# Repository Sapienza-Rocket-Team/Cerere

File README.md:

# Cerere
Avionics board for Medusa 2026

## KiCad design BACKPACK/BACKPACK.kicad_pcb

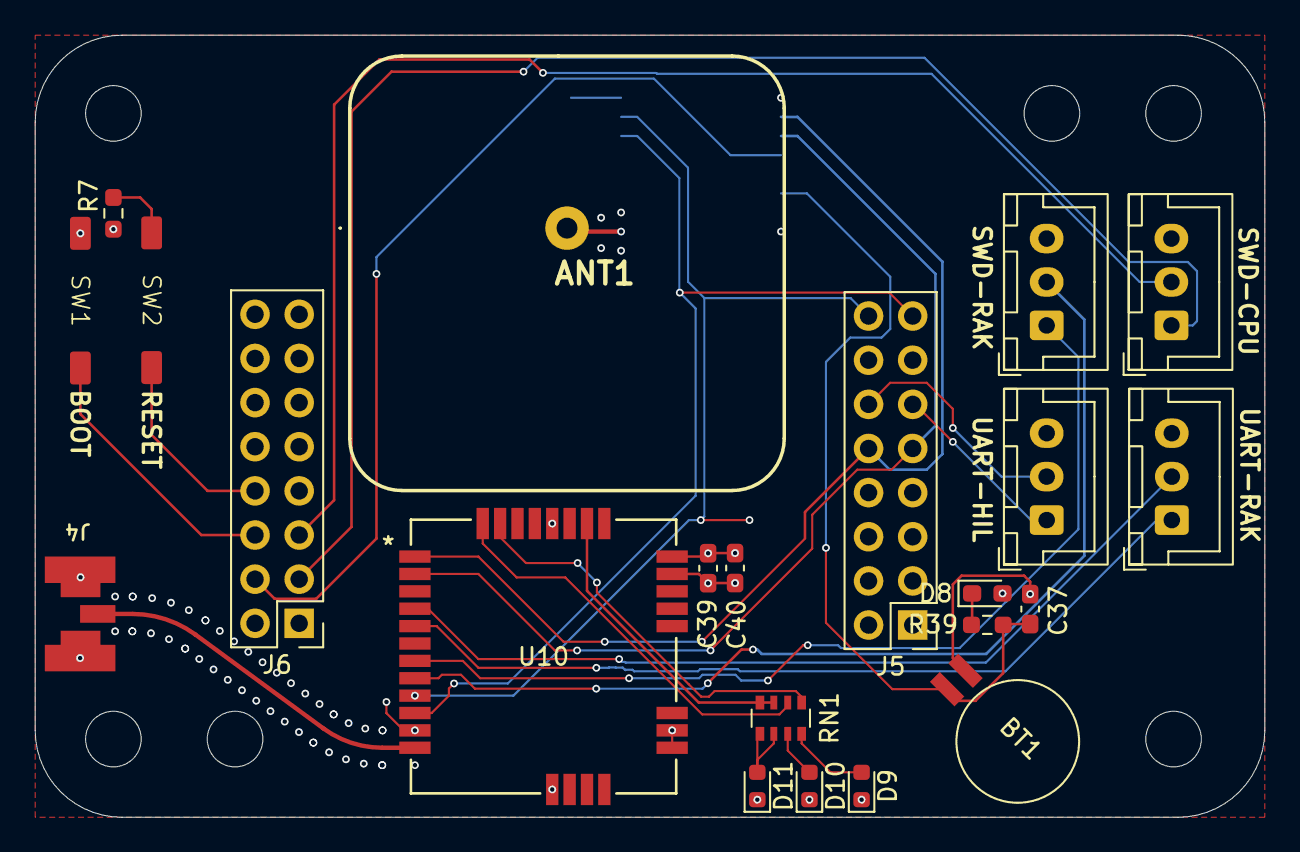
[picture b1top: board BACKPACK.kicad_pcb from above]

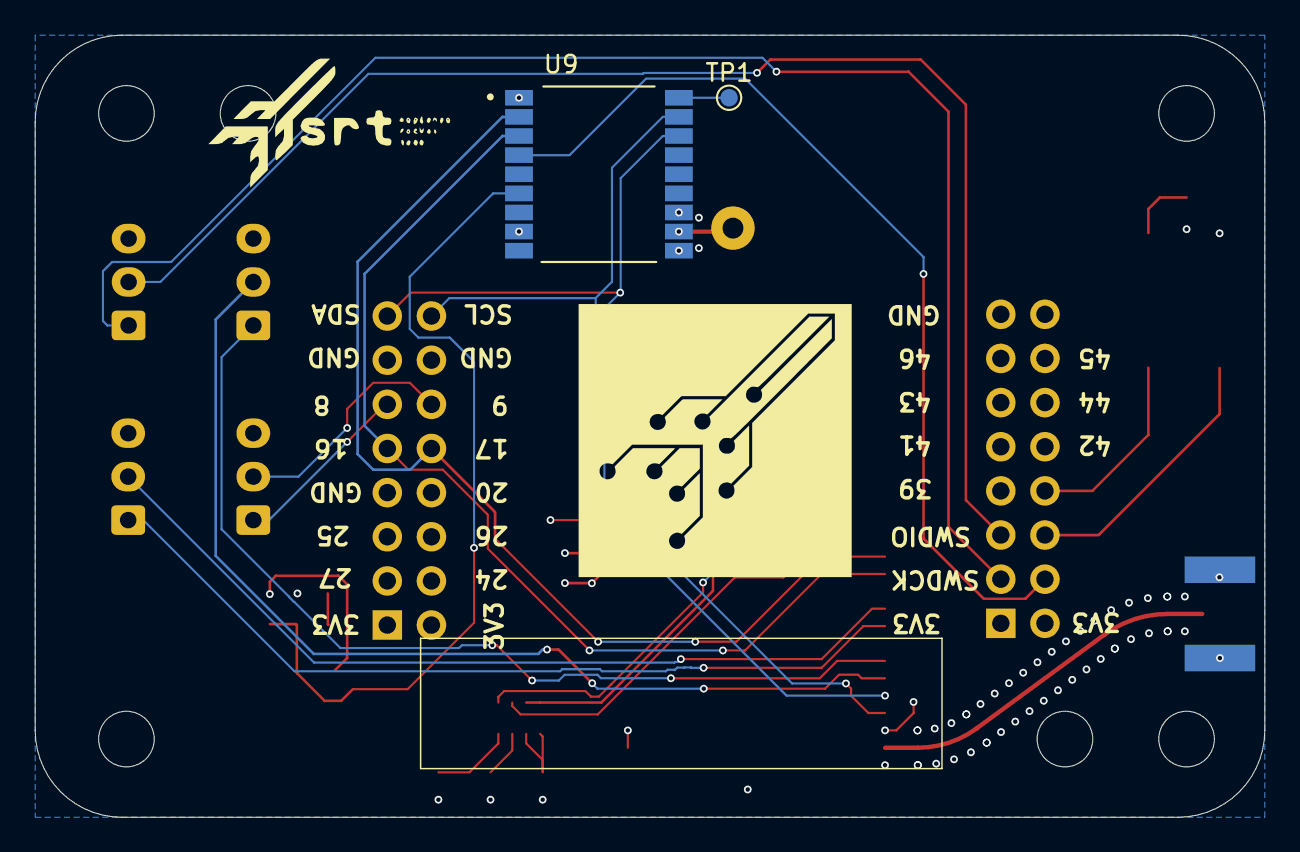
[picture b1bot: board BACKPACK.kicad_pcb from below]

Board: 4 copper layers, 70.8 x 45.0 mm, 30 parts (8 on the bottom side), 29 nets.

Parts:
ANT1: AANI-PP-0055; AANIPP0055
BT1: Battery_Cell; BatteryHolder_Seiko_MS621F
C37, C40: 100nF; C_0603_1608Metric_Pad1.08x0.95mm_HandSolder
C39: 10nF; C_0603_1608Metric_Pad1.08x0.95mm_HandSolder
D8: D_Schottky_Small; D_0603_1608Metric_Pad1.05x0.95mm_HandSolder
D9: BLUE; LED_0603_1608Metric
D10: GREEN; LED_0603_1608Metric
D11: RED; LED_0603_1608Metric
H1, H2, H3, H4, H5, H6: MountingHole; MountingHole_3.2mm_M3
J1, J2, J3, J7: Conn_01x03_Pin; JST_XH_B3B-XH-A_1x03_P2.50mm_Vertical
J4: Conn_Coaxial; SMA_EDGE__UFL
J5, J6: Conn_02x08_Odd_Even; PinHeader_2x08_P2.54mm_Vertical
R7: 1k; R_0603_1608Metric_Pad0.98x0.95mm_HandSolder
R39: 47k; R_0603_1608Metric_Pad0.98x0.95mm_HandSolder
RN1: 220; R_Array_Convex_4x0603
SW1: BOOTSEL; TSB008
SW2: RESET; TSB008
TP1: TestPoint; TestPoint_Pad_D1.0mm
U9: TESEO-LIV4F; XCVR_TESEO-LIV4F
U10: RAK3172; RAK3172_RAK

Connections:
+3V3: C39.1, C40.1, D8.2 (A), J5.1, J5.2, J6.1, J6.2, U9.8 (VCC), U10.24 (VDD)
/BOOTSEL: J6.6, SW1.2
/CPU_SWDCLK: J2.1, J6.3
/CPU_SWDIO: J2.2, J6.5
/L_BLUE: RN1.1 (R1.1), U10.31 (PB4/ADC2)
/L_GREEN: RN1.2 (R2.1), U10.32 (PB3/ADC1)
/L_RED: RN1.3 (R3.1), RN1.4 (R4.1), U10.26 (PB2/AD3)
/RESET: J6.8, SW2.2
/RX_GPS: J5.9, U9.3 (UART-RX), U10.2 (PA2/UART2_TX)
/SCL_RADIO: J5.16, U9.17 (I2C_SCL), U10.9 (PA12/I2C_SCL)
/SDA_RADIO: J5.15, U9.16 (I2C_SDA), U10.10 (PA11/I2C_SDA)
/SWCLK: J3.2, U10.8 (PA14/SWCLK)
/SWDIO: J3.1, U10.7 (PA13/SWDIO)
/TX_GPS: J5.10, U9.2 (UART-TX), U10.1 (PA3/UART2_RX)
/UART1_RX_RADIO: J7.1, U10.5 (PB7/UART1_RX)
/UART1_TX_RADIO: J7.2, U10.4 (PB6/UART1_TX)
ANT: J4.1 (In), U10.12 (RF)
GND: BT1.2 (-), C37.2, C39.2, C40.2, D9.1 (K), D10.1 (K), D11.1 (K), J1.3, J2.3, J3.3, J4.2 (Ext), J5.7, J5.13, J5.14, J6.15, J6.16, J7.3, R7.1, SW1.1, U9.1 (GND), U9.10 (GND_RF), U9.12 (GND_RF__1), U10.11 (GND), U10.17 (GND), U10.18 (GND), U10.23 (GND), U10.28 (GND)
HIL_RX: J1.2, J5.12
HIL_TX: J1.1, J5.11
unnamed: BT1.1 (+), C37.1, R39.2, U9.6 (VBAT)
unnamed: D8.1 (K), R39.1
unnamed: D9.2 (A), RN1.8 (R1.2)
unnamed: D10.2 (A), RN1.7 (R2.2)
unnamed: D11.2 (A), RN1.5 (R4.2), RN1.6 (R3.2)
unnamed: R7.2, SW2.1
unnamed: TP1.1, U9.18 (PRG)
unnamed: ANT1.1, U9.11 (RF_IN)
PPS: J6.4, U9.4 (PPS)

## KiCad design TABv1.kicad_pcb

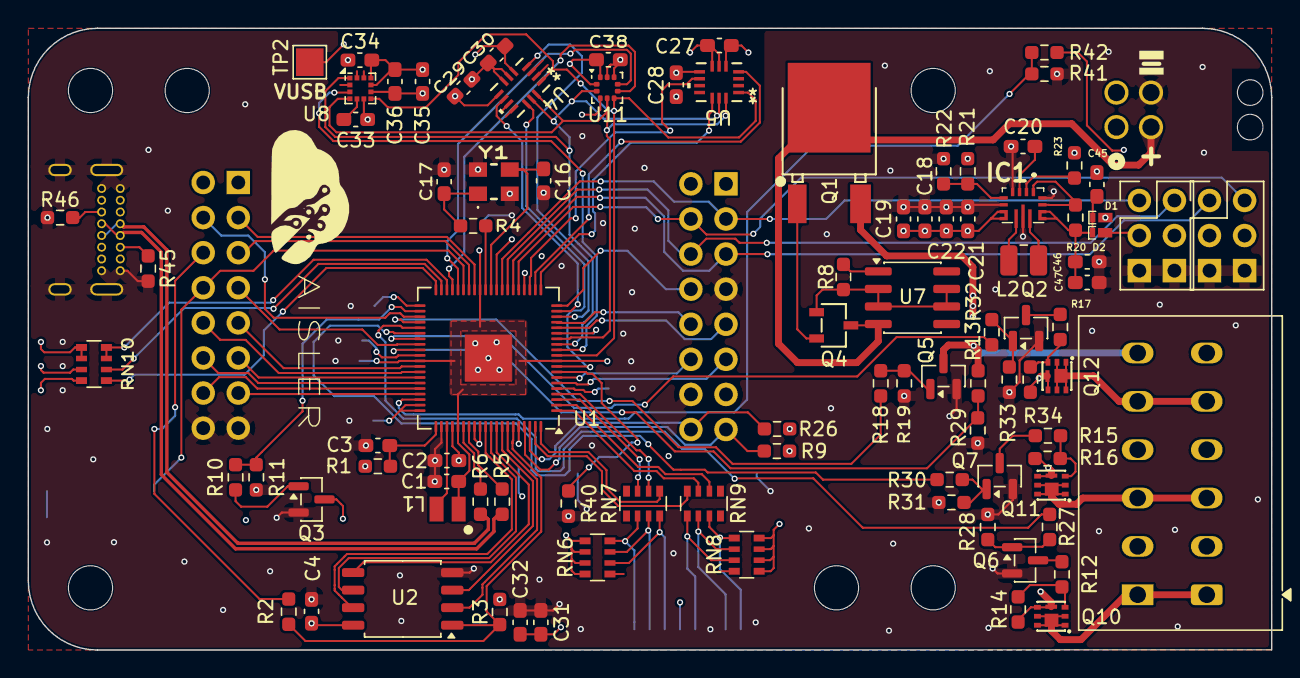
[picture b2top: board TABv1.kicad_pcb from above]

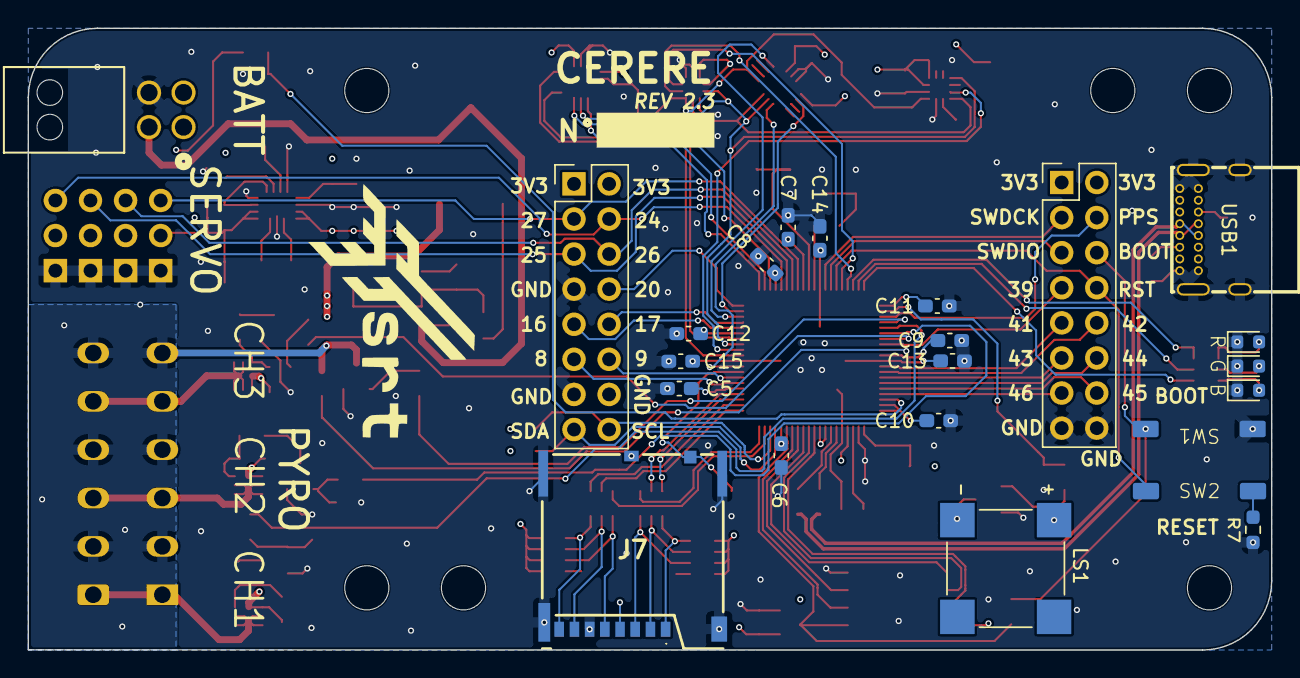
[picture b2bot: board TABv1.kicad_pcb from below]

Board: 4 copper layers, 90.0 x 45.0 mm, 122 parts (23 on the bottom side), 112 nets.

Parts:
C1, C2, C3: 4.7uF; C_0603_1608Metric_Pad1.08x0.95mm_HandSolder
C4, C5, C6, C7, C8, C9, C10, C11, C12, C13, C14, C15: 100n; C_0603_1608Metric_Pad1.08x0.95mm_HandSolder
C16, C17: 15pF; C_0603_1608Metric_Pad1.08x0.95mm_HandSolder
C18, C19, C22: 22uF; C_0603_1608Metric_Pad1.08x0.95mm_HandSolder
C20, C27, C28, C29, C30, C31, C38: 100nF; C_0603_1608Metric_Pad1.08x0.95mm_HandSolder
C21, C32, C35, C45, C46, C47: 10uF; C_0603_1608Metric_Pad1.08x0.95mm_HandSolder
C33: 220nF; C_0603_1608Metric_Pad1.08x0.95mm_HandSolder
C34, C36: 100nf; C_0603_1608Metric_Pad1.08x0.95mm_HandSolder
D1, D2: D_Schottky_Small; SDM2U30CSP
D5: BLUE; LED_0603_1608Metric
D6: GREEN; LED_0603_1608Metric
D7: RED; LED_0603_1608Metric
H1, H2, H3, H4, H5, H6: MountingHole; MountingHole_3.2mm_M3
IC1: TPS630702RNMR; TPS630701RNMR
J5, J6: Conn_02x08_Odd_Even; PinHeader_2x08_P2.54mm_Vertical
J7: 503398-1892; 5033981892
J8: 1053141104; CONN_SD-105314-100_04_MOL
J9, J10: Conn_02x03_Odd_Even; PinHeader_2x03_P2.54mm_Vertical
J11: Conn_01x06_Pin; TerminalBlock_WAGO_2601-1106_1x06_P3.50mm_Horizontal
L1: 3.3uh directional; L_AOTA-B201610S3R3-101-T_MCH
L2: 1.5uh; L_1008_2520Metric
LS1: CMT-8503-85B-SMT-TR; XDCR_CMT-8503-85B-SMT-TR
Q1: MJD44H11T4G; TO-252-2_L6.5-W6.1-P4.58-LS10.0-TL
Q2, Q3, Q5, Q6, Q7: DMN2040U; SOT-23
Q4: BC817-25,215; SOT-23-3_L2.9-W1.6-P1.90-LS2.8-BR
Q10, Q11, Q12: PJM09P30DF; DFN-6_L2.0-W2.0-P0.65-BL-EP-1
R1: 33; R_0603_1608Metric_Pad0.98x0.95mm_HandSolder
R2, R4, R7, R12, R15, R17: 1k; R_0603_1608Metric_Pad0.98x0.95mm_HandSolder
R3, R14, R16, R19, R20, R28, R29, R31, R33, R34, R40, R41: 10k; R_0603_1608Metric_Pad0.98x0.95mm_HandSolder
R5, R6: 27; R_0603_1608Metric_Pad0.98x0.95mm_HandSolder
R8: 430; R_0603_1608Metric_Pad0.98x0.95mm_HandSolder
R9, R26: 4.7k; R_0603_1608Metric_Pad0.98x0.95mm_HandSolder
R10, R18, R27, R30, R32: 100; R_0603_1608Metric_Pad0.98x0.95mm_HandSolder
R11: 10K; R_0603_1608Metric_Pad0.98x0.95mm_HandSolder
R13, R42: 40k; R_0603_1608Metric_Pad0.98x0.95mm_HandSolder
R21: 470k; R_0603_1608Metric_Pad0.98x0.95mm_HandSolder
R22: 150k; R_0603_1608Metric_Pad0.98x0.95mm_HandSolder
R23: 100k; R_0603_1608Metric_Pad0.98x0.95mm_HandSolder
R45, R46: 5.1k; R_0603_1608Metric_Pad0.98x0.95mm_HandSolder
RN6, RN8: 24k; R_Array_Convex_4x0603
RN7, RN9: 47; R_Array_Convex_4x0603
RN10: 220; R_Array_Convex_4x0603
SW1: BOOTSEL; TSB008
SW2: RESET; TSB008
TP2: TestPoint; TestPoint_Pad_2.0x2.0mm
U1: RP2350B-QFN80; QFN-80-1EP_10x10mm_P0.4mm_EP3.4x3.4mm
U2: W25Q128JVS; SOIC-8_5.3x5.3mm_P1.27mm
U4, U5: LSM6DSV80XTR; QFN_LSM6DSV80XTR_STM
U7: LM334M; SOIC-8_3.9x4.9mm_P1.27mm
U8: LIS2MDL; LGA-12_2x2mm_P0.5mm
U11: LPS22DF; ST_HLGA-10_2x2mm_P0.5mm_LayoutBorder3x2y
USB1: TYPEC-306DDW-ARP16; USB-C-TH_UC23-0B16F00P11
Y1: 12MHz; ABM8272T3

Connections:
+1V1: C1.1, C13.2, C14.2, C15.2, L1.1, U1.10 (DVDD), U1.32 (DVDD), U1.51 (DVDD), U1.65 (VREG_FB)
+3V3: C2.1, C4.1, C5.2, C6.2, C7.2, C8.2, C9.2, C10.2, C11.2, C12.2, C18.1, C19.1, C21.2, C22.1, C27.2, C28.2, C29.2, C30.2, C31.1, C32.2, C34.1, C35.1, C36.2, C38.1, IC1.7 (VOUT_1), IC1.8 (VOUT_2), J5.1, J5.2, J6.1, J6.2, J7.4 (VDD), J7.10 (DETECT_SWITCH), LS1.P, R1.2, R3.1, R9.2, R21.2, R23.1, R26.2, RN6.5 (R4.2), RN6.6 (R3.2), RN6.7 (R2.2), RN6.8 (R1.2), RN8.1 (R1.1), RN8.2 (R2.1), RN8.3 (R3.1), RN8.4 (R4.1), U1.5 (IOVDD), U1.15 (IOVDD), U1.24 (IOVDD), U1.29 (IOVDD), U1.41 (IOVDD), U1.50 (IOVDD), U1.59 (ADC_AVDD), U1.60 (IOVDD), U1.64 (VREG_VIN), U1.68 (USB_OTP_VDD), U1.69 (QSPI_IOVDD), U1.76 (IOVDD), U2.8 (VCC), U4.5, U4.8, U5.5, U5.8, U8.9 (Vdd), U8.10 (Vdd_IO), U11.1 (Vdd_IO), U11.10 (VDD)
+BATT: D2.2 (A), J8.3, J9.3, J9.4, J10.3, J10.4, Q1.4 (C), Q4.3, R42.2, U7.4
/AVDD: C3.2, R1.1, U1.61 (VREG_AVDD)
/BARO_CS: U1.37 (GPIO29), U11.6 (~CS)
/BARO_INT: U1.36 (GPIO28), U11.7 (INT_DRDY)
/BATT_SENSE: R41.2, R42.1, U1.58 (GPIO47_ADC7)
/BUZZ: R10.1, R11.2, U1.42 (GPIO33)
/GPIO20: J5.8, U1.20 (GPIO20)
/GPIO39: J6.7, U1.48 (GPIO39)
/GPIO41: J6.9, U1.52 (GPIO41_ADC1)
/GPIO42: J6.10, U1.53 (GPIO42_ADC2)
/GPIO43: J6.11, U1.54 (GPIO43_ADC3)
/GPIO44: J6.12, U1.55 (GPIO44_ADC4)
/GPIO45: J6.14, U1.56 (GPIO45_ADC5)
/GPIO46: J6.13, U1.57 (GPIO46_ADC6)
/IMU45_CS: U1.9 (GPIO11), U4.12
/IMU45_INT1: U1.18 (GPIO18), U4.4
/IMU45_INT2: U1.19 (GPIO19), U4.9
/IMU_CS: U1.21 (GPIO21), U5.12
/IMU_INT1: U1.22 (GPIO22), U5.4
/IMU_INT2: U1.23 (GPIO23), U5.9
/LX: L1.2, U1.63 (VREG_LX)
/L_BLUE: RN10.1 (R1.1), U1.40 (GPIO32)
/L_GREEN: RN10.2 (R2.1), U1.39 (GPIO31)
/L_RED: RN10.3 (R3.1), RN10.4 (R4.1), U1.38 (GPIO30)
/MAG_CS: U1.12 (GPIO13), U8.3 (~CS)
/PWM1: J5.4, J10.2, U1.25 (GPIO24)
/PWM2: J5.5, J10.1, U1.26 (GPIO25)
/PWM3: J5.6, J9.2, U1.27 (GPIO26)
/PWM4: J5.3, J9.1, U1.28 (GPIO27)
/PYRO_ENABLE: R18.1, U1.44 (GPIO35)
/PYRO_FIRE_1: R27.1, U1.45 (GPIO36)
/PYRO_FIRE_2: R30.1, U1.46 (GPIO37)
/PYRO_FIRE_3: R32.1, U1.47 (GPIO38)
/PYRO_SENSE: R13.1, R29.2, U1.49 (GPIO40_ADC0)
/Pyro/PYRO1: J11.1, Q10.1 (D), Q10.2 (D), Q10.5 (D), Q10.6 (D), Q10.7 (D)
/Pyro/PYRO2: J11.3, Q11.1 (D), Q11.2 (D), Q11.5 (D), Q11.6 (D), Q11.7 (D)
/Pyro/PYRO3: J11.5, Q12.1 (D), Q12.2 (D), Q12.5 (D), Q12.6 (D), Q12.7 (D)
/Pyro/PYRO_HIGH: Q1.3 (E), Q10.4 (S), Q10.8 (S), Q11.4 (S), Q11.8 (S), Q12.4 (S), Q12.8 (S), R14.2, R16.2, R34.2
/Pyro/PYRO_LOW: J11.2, J11.4, J11.6, Q5.3 (D), R13.2
/RESET: J6.8, SW2.2, U1.35 (RUN)
/RX_GPS: J5.9, U1.16 (GPIO16)
/SCLK: U1.71 (QSPI_SCLK), U2.6 (CLK)
/SCL_RADIO: J5.16, R26.1, U1.78 (GPIO1)
/SD0: U1.72 (QSPI_SD0), U2.5 (DI/IO_{0})
/SD1: U1.74 (QSPI_SD1), U2.2 (DO/IO_{1})
/SD2: U1.73 (QSPI_SD2), U2.3 (~WP/IO_{2})
/SD3: U1.70 (QSPI_SD3), U2.7 (~HOLD/~RESET/IO_{3})
/SDA_RADIO: J5.15, R9.1, U1.77 (GPIO0)
/SD_CLK: RN7.4 (R4.1), U1.79 (GPIO2)
/SD_CMD: RN9.1 (R1.1), U1.80 (GPIO3)
/SD_DAT0: RN7.3 (R3.1), U1.1 (GPIO4)
/SD_DAT1: RN7.2 (R2.1), U1.2 (GPIO5)
/SD_DAT2: RN9.3 (R3.1), U1.3 (GPIO6)
/SD_DAT3: RN9.2 (R2.1), U1.4 (GPIO7)
/SD_detect: J7.9 (DETECT_LEVER), R40.2, U1.8 (GPIO10)
/SPI1.CK: U1.13 (GPIO14), U4.13, U5.13, U8.1 (SCL/SPC), U11.2 (SCL)
/SPI1.RX: U1.11 (GPIO12), U4.1, U5.1, U8.7 (DRDY), U11.5 (SA0)
/SPI1.TX: U1.14 (GPIO15), U4.14, U5.14, U8.4 (SDA/SDI/SDO), U11.4 (SDA)
/SS: R2.2, R3.2, U1.75 (QSPI_SS), U2.1 (~CS)
/SWDCLK: J6.3, U1.33 (SWCLK)
/SWDIO: J6.5, U1.34 (SWDIO)
/TX_GPS: J5.10, U1.17 (GPIO17)
/XIN: C16.2, U1.30 (XIN), Y1.3
/XOUT: R4.1, U1.31 (XOUT)
/microSD/_CLK: J7.5 (CLK), RN7.5 (R4.2), RN8.7 (R2.2)
/microSD/_CMD: J7.3 (CMD), RN6.2 (R2.1), RN9.8 (R1.2)
/microSD/_DAT0: J7.7 (DAT0), RN7.6 (R3.2), RN8.6 (R3.2)
/microSD/_DAT1: J7.8 (DAT1), RN7.7 (R2.2), RN8.5 (R4.2)
/microSD/_DAT2: J7.1 (DAT2), RN6.4 (R4.1), RN9.6 (R3.2)
/microSD/_DAT3: J7.2 (CD/DAT3), RN6.3 (R3.1), RN9.7 (R2.2)
BOOTSEL: J6.6, R2.1, SW1.2
D+: R5.2, USB1.A6 (DP1), USB1.B6 (DP2)
D-: R6.2, USB1.A7 (DN1), USB1.B7 (DN2)
GND: C1.2, C2.2, C3.1, C4.2, C5.1, C6.1, C7.1, C8.1, C9.1, C10.1, C11.1, C12.1, C13.1, C14.1, C15.1, C16.1, C17.1, C18.2, C19.2, C20.1, C21.1, C22.2, C27.1, C28.1, C29.1, C30.1, C31.2, C32.1, C33.2, C34.2, C35.2, C36.1, C38.2, C45.1, C46.2, C47.2, D5.1 (K), D6.1 (K), D7.1 (K), IC1.4 (GND), IC1.6 (FB2), IC1.10 (PGND), IC1.15 (VSEL), J5.7, J5.13, J5.14, J6.15, J6.16, J7.6 (VSS), J7.11, J7.12, J7.13, J7.14, J8.4, J9.5, J9.6, J10.5, J10.6, Q2.2 (S), Q3.2 (S), Q5.2 (S), Q6.2 (S), Q7.2 (S), R7.1, R11.1, R19.1, R22.1, R28.1, R29.1, R31.1, R33.1, R40.1, R41.1, R45.2, R46.2, SW1.1, U1.62 (VREG_PGND), U1.81 (GND), U2.4 (GND), U4.6, U4.7, U5.6, U5.7, U8.6 (GND), U8.8 (GND), U11.3 (GND), U11.8 (GND_IO), U11.9 (GND), USB1.17 (EH), USB1.18 (EH), USB1.19 (EH), USB1.20 (EH), USB1.A1 (GND), USB1.A12 (GND), USB1.B1 (GND), USB1.B12 (GND), Y1.2, Y1.4
HIL_RX: J5.12, U1.7 (GPIO9)
HIL_TX: J5.11, U1.6 (GPIO8)
unnamed: C17.2, R4.2, Y1.1
unnamed: C45.2, C46.1, C47.1, D1.1 (K), D2.1 (K), IC1.12 (VIN_1), IC1.13 (VIN_2), R20.2
unnamed: D5.2 (A), RN10.8 (R1.2)
unnamed: D6.2 (A), RN10.7 (R2.2)
unnamed: D7.2 (A), RN10.5 (R4.2), RN10.6 (R3.2)
unnamed: IC1.5 (FB), R21.1, R22.2
unnamed: IC1.11 (L1), L2.2
unnamed: IC1.9 (L2), L2.1
unnamed: C20.2, IC1.3 (VAUX)
unnamed: Q1.1 (B), Q4.2
unnamed: Q2.3 (D), R17.1
unnamed: Q2.1 (G), R32.2, R33.2
unnamed: LS1.N, Q3.3 (D)
unnamed: Q3.1 (G), R10.2
unnamed: Q4.1, R8.2, U7.2, U7.3, U7.6, U7.7
unnamed: Q5.1 (G), R18.2, R19.2
unnamed: Q6.3 (D), R12.1
unnamed: Q6.1 (G), R27.2, R28.2
unnamed: Q7.3 (D), R15.1
unnamed: Q7.1 (G), R30.2, R31.2
unnamed: Q10.3 (G), R12.2, R14.1
unnamed: Q11.3 (G), R15.2, R16.1
unnamed: Q12.3 (G), R17.2, R34.1
unnamed: R7.2, SW2.1
unnamed: R8.1, U7.1
unnamed: R6.1, U1.66 (USB_DM)
unnamed: R5.1, U1.67 (USB_DP)
unnamed: C33.1, U8.5 (C1)
unnamed: R45.1, USB1.A5 (CC1)
unnamed: R46.1, USB1.B5 (CC2)
PG: IC1.2 (PG), R23.2
PPS: J6.4, U1.43 (GPIO34)
SYNC: IC1.1 (PS/SYNC), IC1.14 (EN), R20.1
VUSB: D1.2 (A), TP2.1 (1_1), USB1.A4 (VBUS), USB1.A9 (VBUS), USB1.B4 (VBUS), USB1.B9 (VBUS)

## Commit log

2026-02-20 primo commit
2026-02-20 perché non funziona
2026-02-20 spostamento connettori
2026-02-21 connettori adattati
2026-02-21 aggiornamenti rev 1.1
2026-02-22 robe di sabato che mi sono dimenticato di pushare
2026-02-28 fpc connector inizio
2026-02-28 spostato hardware in the loop a connettore fpc e fixata etichetta bootsel
2026-03-01 fpc connector update
2026-03-04 inizio rev 2.0
2026-03-05 Tentativo di Sbroglio
2026-03-06 connessione 1v1 sotto il rp2350 come la fa raspberry pi, tracce con l impedenza corretta sulla usb, aggiunto collegamenti mancanti e un pò di drc
2026-03-06 fixed the connectors, rearranged sensors and fixed a bit the silkscreen
2026-03-06 small fixes, started working on the backpack
2026-03-07 aiuto
2026-03-07 Cristo risorto
2026-03-07 ficato connetotore wagoi se negro
2026-03-14 neon ha detto pusha
2026-03-14 secondo push
2026-03-14 Ordered
2026-03-27 constrains fix
2026-03-27 rerouting 0.15mm piste
2026-03-28 nuovo routing completato (piste 0.15mm)
2026-03-28 USB impeadance matching, silkscreen fix, and routing improvement
2026-03-28 fine rev 2.2
2026-04-01 Ordine 1 Aprile
2026-04-25 TPS cap added
2026-04-25 Aggiunta GNDPlane
